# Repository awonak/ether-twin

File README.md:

# Ether Twin

A platform for sharing control voltage and audio over RJ45 shielded network cable

Note: These modules are still a work in progress and may contain errors.

## Ether Twin v1 - Stand-alone

Stand-alone passive desktop version.

Follow the ibom component placement guide [here](https://htmlpreview.github.io/?https://github.com/awonak/ether-twin/blob/main/ether_v1/bom/ibom.html).

Step by step build guide [here](ether_v1/README.md).

## Ether Twin v2 - 3U

Rack mount 3U 10HP version

*Photo Coming Soon*

## Ether Mix - Stand-alone

Stand-alone passive mixer

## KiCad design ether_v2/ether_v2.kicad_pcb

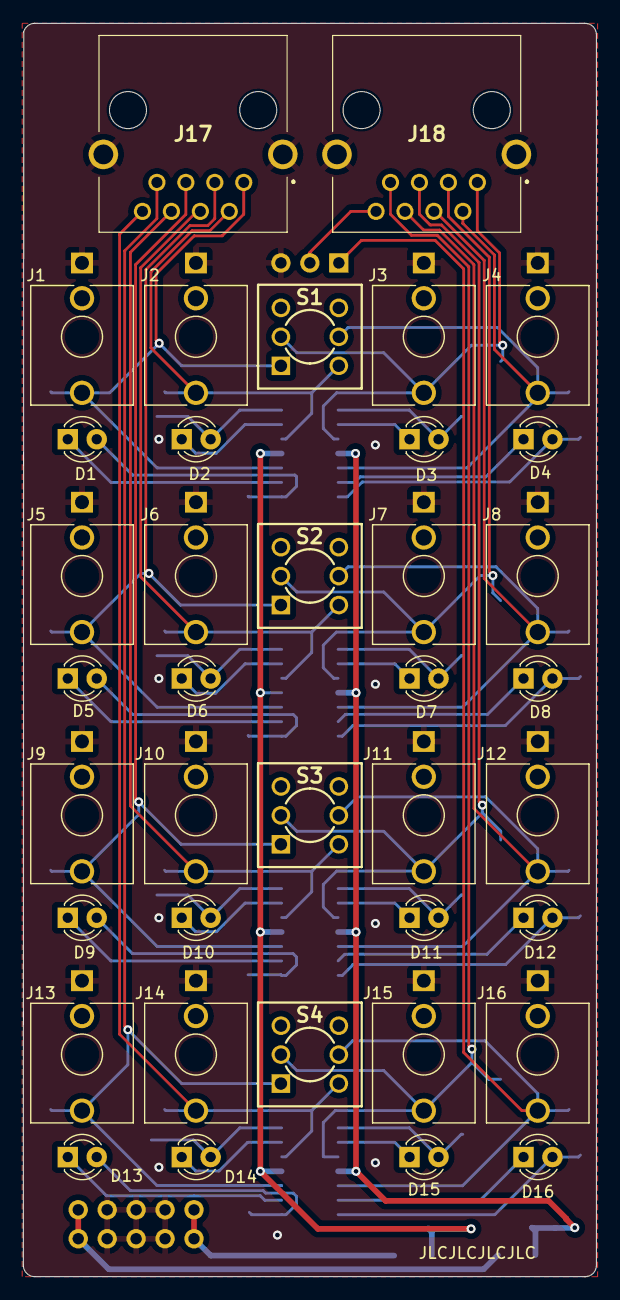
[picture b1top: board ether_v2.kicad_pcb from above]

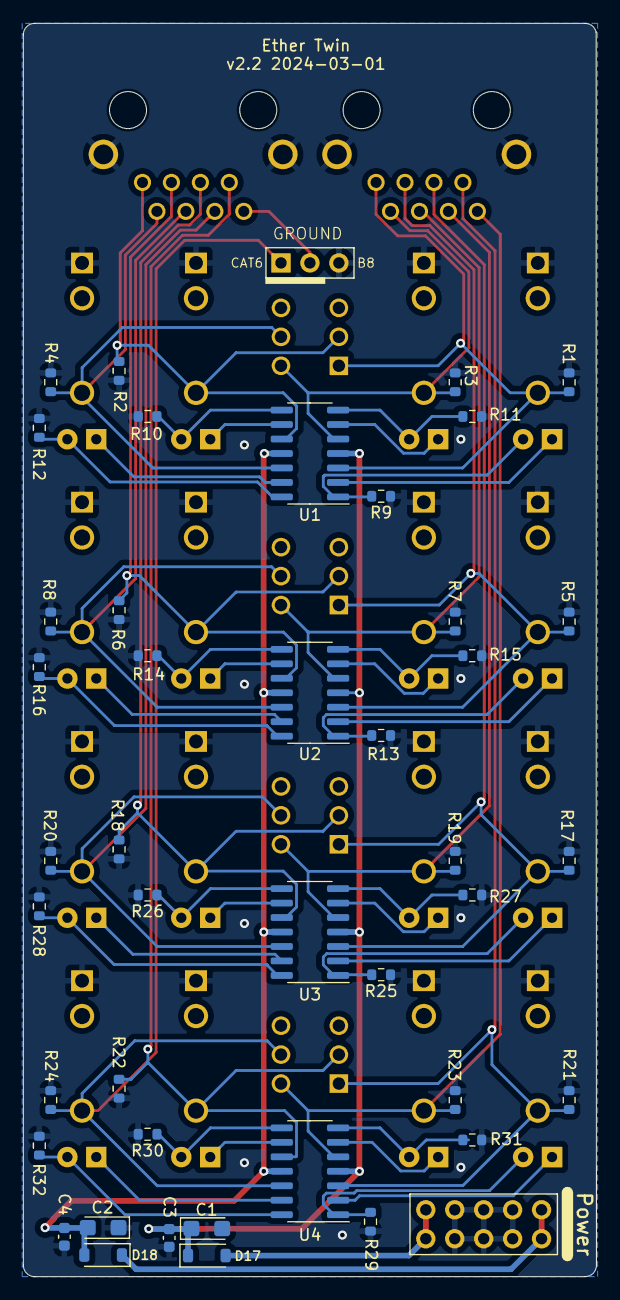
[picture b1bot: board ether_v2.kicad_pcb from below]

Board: 2 copper layers, 50.3 x 110.0 mm, 82 parts (44 on the bottom side), 54 nets.

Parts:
C1, C2: 10uF; CP_EIA-3216-18_Kemet-A
C3, C4: 100nF; C_0603_1608Metric
D1, D2, D3, D4, D5, D6, D7, D8, D9, D10, D11, D12, D13, D14, D15, D16: LED_Dual_Bidirectional; LED_D3.0mm
D17, D18: 1N5817; D_SOD-123
J1, J2, J3, J4, J5, J6, J7, J8, J9, J10, J11, J12, J13, J14, J15, J16: PJ398SM; Jack_3.5mm_QingPu_WQP-PJ398SM_Vertical_CircularHoles_3dModel
J17, J18: SS65100-024F; SS65100024F
J19: Power; Pins_2x05_2.54mm_TH_Europower
J20: Conn_01x03; PinHeader_1x03_P2.54mm_Vertical
R1, R2, R3, R4, R5, R6, R7, R8, R17, R18, R19, R20, R21, R22, R23, R24: 100K; R_0603_1608Metric
R9, R10, R11, R12, R13, R14, R15, R16, R25, R26, R27, R28, R29, R30, R31, R32: 470; R_0603_1608Metric
S1, S2, S3, S4: 2MD1T1B1M2QES
U1, U2, U3, U4: TL074; SO-14_3.9x8.65mm_P1.27mm

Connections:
+12V: C1.1, C3.1, D17.1 (K), U1.4 (V+), U2.4 (V+), U3.4 (V+), U4.4 (V+)
-12V: C2.2, C4.2, D18.2 (A), U1.11 (V-), U2.11 (V-), U3.11 (V-), U4.11 (V-)
A1: J1.T, J17.1, R1.2, S1.1 (A), U1.3 (+)
A2: J2.T, J17.2, R3.2, S1.4 (A), U1.5 (+)
A3: J5.T, J17.3, R5.2, S2.1 (A), U2.3 (+)
A4: J6.T, J17.4, R7.2, S2.4 (A), U2.5 (+)
A5: J9.T, J17.5, R17.2, S3.1 (A), U3.3 (+)
A6: J10.T, J17.6, R19.2, S3.4 (A), U3.5 (+)
A7: J13.T, J17.7, R21.2, S4.1 (A), U4.3 (+)
A8: J14.T, J17.8, R23.2, S4.4 (A), U4.5 (+)
B1: J3.T, J18.1, R2.2, S1.2 (B), U1.10 (+)
B2: J4.T, J18.2, R4.2, S1.5 (B), U1.12 (+)
B3: J7.T, J18.3, R6.2, S2.2 (B), U2.10 (+)
B4: J8.T, J18.4, R8.2, S2.5 (B), U2.12 (+)
B5: J11.T, J18.5, R18.2, S3.2 (B), U3.10 (+)
B6: J12.T, J18.6, R20.2, S3.5 (B), U3.12 (+)
B7: J15.T, J18.7, R22.2, S4.2 (B), U4.10 (+)
B8: J18.8, J20.2
GND: C1.2, C2.1, C3.2, C4.1, J1.S, J2.S, J3.S, J4.S, J5.S, J6.S, J7.S, J8.S, J9.S, J10.S, J11.S, J12.S, J13.S, J14.S, J15.S, J16.S, J17.9, J17.10, J18.9, J18.10, J19.3 (GND), J19.4 (GND), J19.5 (GND), J19.6 (GND), J19.7 (GND), J19.8 (GND), J20.3, R1.1, R2.1, R3.1, R4.1, R5.1, R6.1, R7.1, R8.1, R9.1, R10.2, R11.1, R12.2, R13.1, R14.2, R15.1, R16.2, R17.1, R18.1, R19.1, R20.1, R21.1, R22.1, R23.1, R24.1, R25.1, R26.2, R27.1, R28.2, R29.1, R30.2, R31.1, R32.2
unnamed: D1.2 (A), R9.2, U1.1
unnamed: D1.1 (K), U1.2 (-)
unnamed: D2.2 (A), R11.2, U1.7
unnamed: D2.1 (K), U1.6 (-)
unnamed: D3.2 (A), R10.1, U1.8
unnamed: D3.1 (K), U1.9 (-)
unnamed: D4.2 (A), R12.1, U1.14
unnamed: D4.1 (K), U1.13 (-)
unnamed: D5.2 (A), R13.2, U2.1
unnamed: D5.1 (K), U2.2 (-)
unnamed: D6.2 (A), R15.2, U2.7
unnamed: D6.1 (K), U2.6 (-)
unnamed: D7.2 (A), R14.1, U2.8
unnamed: D7.1 (K), U2.9 (-)
unnamed: D8.2 (A), R16.1, U2.14
unnamed: D8.1 (K), U2.13 (-)
unnamed: D9.2 (A), R25.2, U3.1
unnamed: D9.1 (K), U3.2 (-)
unnamed: D10.2 (A), R27.2, U3.7
unnamed: D10.1 (K), U3.6 (-)
unnamed: D11.2 (A), R26.1, U3.8
unnamed: D11.1 (K), U3.9 (-)
unnamed: D12.2 (A), R28.1, U3.14
unnamed: D12.1 (K), U3.13 (-)
unnamed: D13.2 (A), R29.2, U4.1
unnamed: D13.1 (K), U4.2 (-)
unnamed: D14.2 (A), R31.2, U4.7
unnamed: D14.1 (K), U4.6 (-)
unnamed: D15.2 (A), R30.1, U4.8
unnamed: D15.1 (K), U4.9 (-)
unnamed: D16.2 (A), R32.1, U4.14
unnamed: D16.1 (K), U4.13 (-)
unnamed: D17.2 (A), J19.1 (+12V), J19.2 (+12V)
unnamed: D18.1 (K), J19.9 (-12V), J19.10 (-12V)
unnamed: J16.T, J20.1, R24.2, S4.5 (B), U4.12 (+)

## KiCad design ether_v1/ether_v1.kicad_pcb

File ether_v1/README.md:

# Ether Twin v1

Tutorial Video:
https://youtu.be/pQHyfLVjiQw?si=90aeZab5XTt6bDr_

## Bill of Materials

| Reference(s) | Qty | Value | Supplier Link |
|-|-|-|-|
| J1 - J16  | 16 | Thonkiconn 3.5mm Mono Jack | https://www.thonk.co.uk/shop/thonkiconn/ |
| J17, J18 | 2 | Ethernet Connectors | https://www.mouser.com/ProductDetail/571-1-406541-5 |
| S1, S2, S3, S4 | 4 | DPDT Switch ON-ON | https://www.thonk.co.uk/shop/sub-mini-toggle-switches/ |
| S5 | 1 | 1PDT Slide Swith ON-ON | https://www.mouser.com/ProductDetail/611-JS102011SAQN |

## Build Guide v1.2

### Solder the components to the main PCB

Follow the ibom component placement guide [here](https://htmlpreview.github.io/?https://github.com/awonak/ether-twin/blob/main/ether_v1/bom/ibom.html).

1. Start by soldering the Ground Select switch S5

1. Place the two Ethernet Jacks. Begin by tacking one mounting hole lug on each Ethernet Jack. Press firmly on the jack while heating the tacked solder to ensure a snug fit.

1. Once the Ethernet Jack lugs are soldered and the jacks are flush against the PCB, then proceed to solder the 8 jack pins. (Pro tip; smear a bit of rosin flux against the pins, then drag a large bead of solder across the pins.)

1. Next, place all 16 cv jacks on the PCB. Attach the top panel, and screw nuts on the 4 corner jacks to hold them in place. Now you can flip the module over and lay it down flat while soldering the cv jacks.

1. (v1.2+ only) Remove the top panel and place the 4 toggle switches. Place the top panel back on and screw on the same 4 corner nut jacks and the 4 switch nuts. Flip the module over and solder the 4 toggle switches. (Either carefully rest the module against one side of the toggle switches, or use a third-hand to hold the module.)

### Assemble the enclosure

1. Remove the top panel attached during the previous step. This will make it easier to attach the standoffs later.

1. Start by threading the loger M3 screws through the 4 mounting holes of the bottom panel.

1. Tighten the M3 nut against those screws.

1. Place the components PCB against the nuts, components facing up.

1. Tighten the 10mm nylon standoffs to the bottom panel screws sticking up from the components PCB.

1. Attach the top panel to the component pcb and screw on all 16 cv jack nuts and 4 toggle switch nuts.

1. Screw the shorter M3 screws into the top panel mounting holes and into the standoffs.

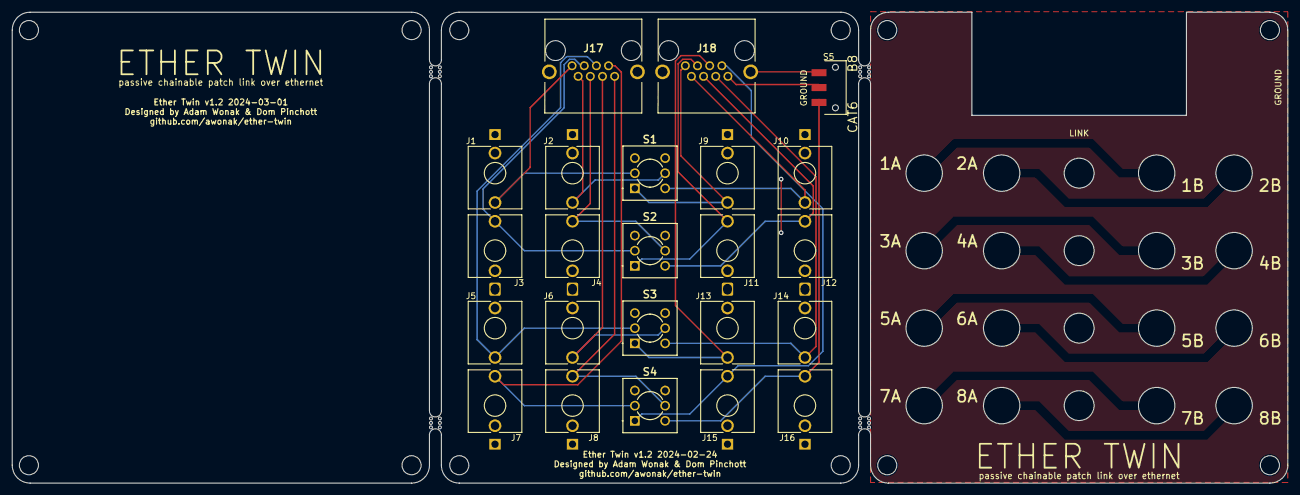
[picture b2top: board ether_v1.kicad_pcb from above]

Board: 2 copper layers, 214.0 x 79.0 mm, 27 parts (0 on the bottom side), 18 nets.

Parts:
J1, J2, J3, J4, J5, J6, J7, J8, J9, J10, J11, J12, J13, J14, J15, J16: AudioJack2_SwitchT; Jack_3.5mm_QingPu_WQP-PJ398SM_Vertical_CircularHoles_3dModel
J17, J18: 1-406541-5; 14065415
MH: VAL**; mouse-bite-2mm-slot
MH#2, MH#3, MH#4: VAL**; mouse-bite-2mm-slot
S1, S2, S3, S4: 2MD1T1B1M2QES
S5: JS102011SAQN; SW_JS102011SAQN

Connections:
A1: J1.T, J17.1, S1.2 (B)
A2: J2.T, J17.2, S1.5 (B)
A3: J3.T, J17.3, S2.2 (B)
A4: J4.T, J17.4, S2.5 (B)
A5: J5.T, J17.5, S3.2 (B)
A6: J6.T, J17.6, S3.5 (B)
A7: J7.T, J17.7, S4.2 (B)
A8: J8.T, J17.8, S4.5 (B)
B1: J9.T, J18.1, S1.1 (A)
B2: J10.T, J18.2, S1.4 (A)
B3: J11.T, J18.3, S2.1 (A)
B4: J12.T, J18.4, S2.4 (A)
B5: J13.T, J18.5, S3.1 (A)
B6: J14.T, J18.6, S3.4 (A)
B7: J15.T, J18.7, S4.1 (A)
B8: J18.8, S5.2
GND: J1.S, J2.S, J3.S, J4.S, J7.S, J8.S, J9.S, J10.S, J11.S, J12.S, J15.S, J16.S, J17.9, J17.10, J18.9, J18.10, S5.3
unnamed: J16.T, S4.4 (A), S5.1

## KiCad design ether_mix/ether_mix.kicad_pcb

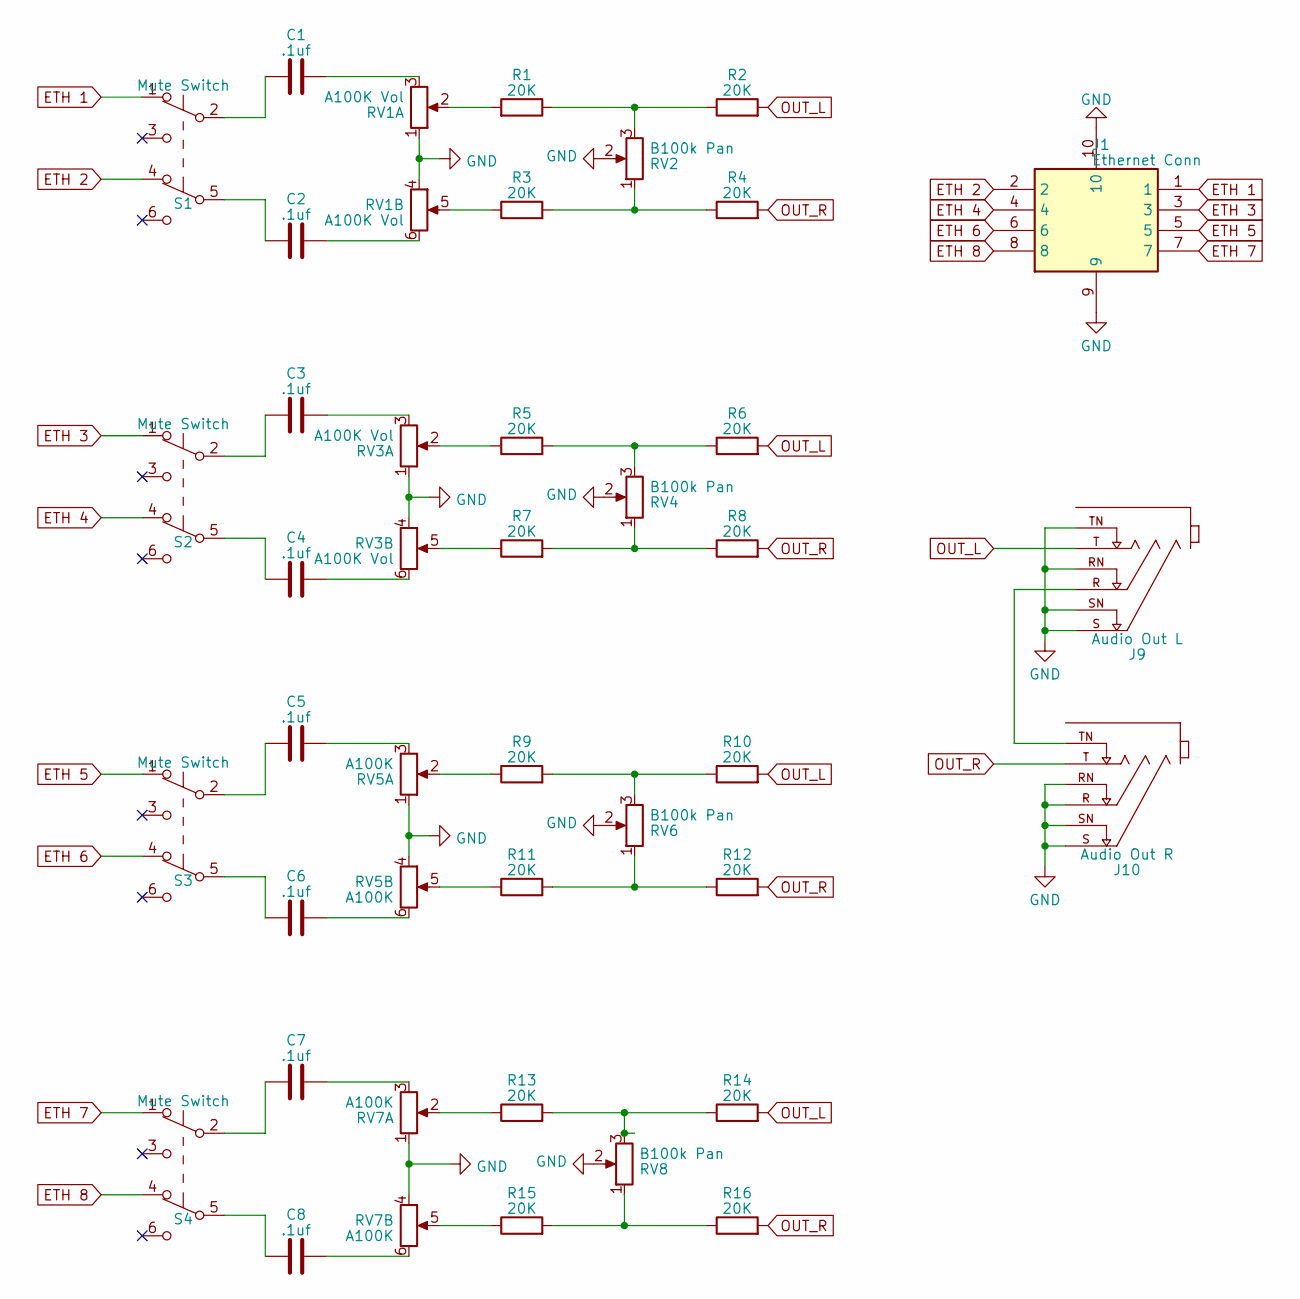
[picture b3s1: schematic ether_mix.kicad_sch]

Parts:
C1, C2, C3, C4, C5, C6, C7, C8: .1uf; C_0603_1608Metric
J1: Ethernet Conn; 14065415; Mouser Part Number 571-1-406541-5
J9: Audio Out L; NEUTRIK_NRJ6HF; PARTREV 19.02.2021
J10: Audio Out R; NEUTRIK_NRJ6HF; PARTREV 19.02.2021
R1, R2, R3, R4, R5, R6, R7, R8, R9, R10, R11, R12, R13, R14, R15, R16: 20K; R_0603_1608Metric
RV1, RV3: A100K Vol; Potentiometer_Alpha_RD902F-40-00D_Dual_Vertical_CircularHol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
RV2, RV4, RV6, RV8: B100k Pan; Potentiometer_Alpha_RD901F-40-00D_Single_Vertical
RV5, RV7: A100K; Potentiometer_Alpha_RD902F-40-00D_Dual_Vertical_CircularHol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
S1, S2, S3, S4: Mute Switch; 2MD1T1B1M2QES; Mouser Part Number 118-2MD1T1B1M2QES

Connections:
ETH 1: J1.1, S1.1 (A)
ETH 2: J1.2, S1.4 (A)
ETH 3: J1.3, S2.1 (A)
ETH 4: J1.4, S2.4 (A)
ETH 5: J1.5, S3.1 (A)
ETH 6: J1.6, S3.4 (A)
ETH 7: J1.7, S4.1 (A)
ETH 8: J1.8, S4.4 (A)
GND: J1.9, J1.10, J9.RN, J9.S, J9.SN, J9.TN, J10.R, J10.RN, J10.S, J10.SN, RV1.1, RV1.4, RV2.2, RV3.1, RV3.4, RV4.2, RV5.1, RV5.4, RV6.2, RV7.1, RV7.4, RV8.2
unnamed: C1.1, S1.2 (B)
unnamed: C1.2, RV1.3
unnamed: C2.1, S1.5 (B)
unnamed: C2.2, RV1.6
unnamed: C3.1, S2.2 (B)
unnamed: C3.2, RV3.3
unnamed: C4.1, S2.5 (B)
unnamed: C4.2, RV3.6
unnamed: C5.1, S3.2 (B)
unnamed: C5.2, RV5.3
unnamed: C6.1, S3.5 (B)
unnamed: C6.2, RV5.6
unnamed: C7.1, S4.2 (B)
unnamed: C7.2, RV7.3
unnamed: C8.1, S4.5 (B)
unnamed: C8.2, RV7.6
unnamed: J9.R, J10.TN
unnamed: R1.1, R2.1, RV2.3
unnamed: R1.2, RV1.2
unnamed: R3.1, RV1.5
unnamed: R3.2, R4.1, RV2.1
unnamed: R5.1, RV3.2
unnamed: R5.2, R6.1, RV4.3
unnamed: R7.1, RV3.5
unnamed: R7.2, R8.1, RV4.1
unnamed: R9.1, RV5.2
unnamed: R9.2, R10.1, RV6.3
unnamed: R11.1, RV5.5
unnamed: R11.2, R12.1, RV6.1
unnamed: R13.1, RV7.2
unnamed: R13.2, R14.1, RV8.3
unnamed: R15.1, RV7.5
unnamed: R15.2, R16.1, RV8.1
OUT_L: J9.T, R2.2, R6.2, R10.2, R14.2
OUT_R: J10.T, R4.2, R8.2, R12.2, R16.2

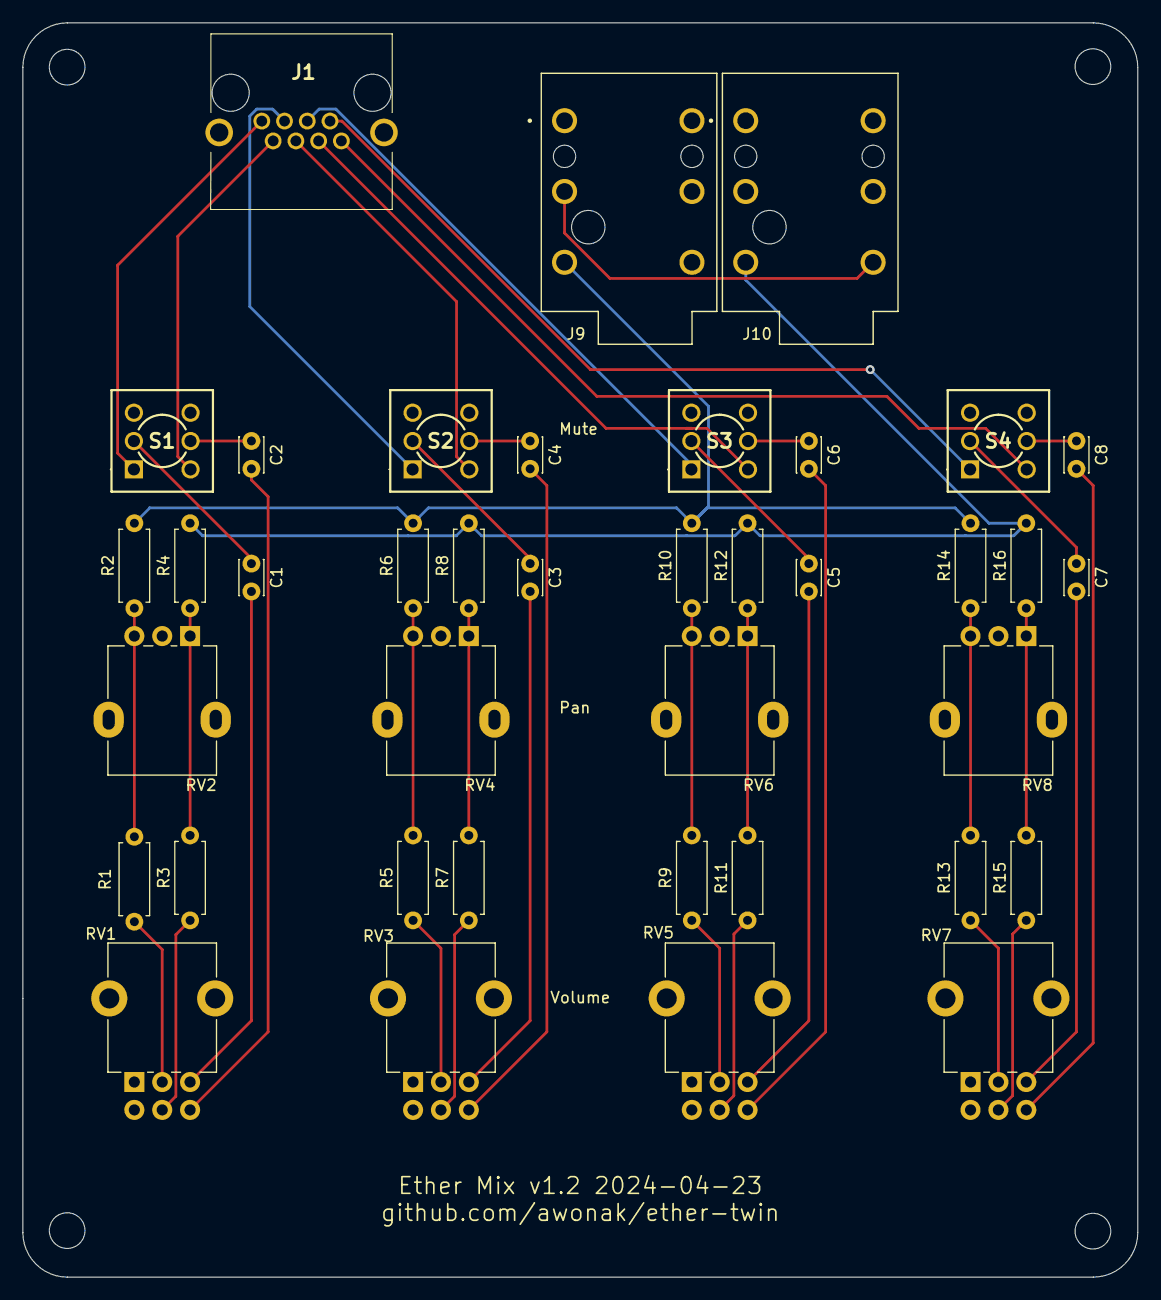
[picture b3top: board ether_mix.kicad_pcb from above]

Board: 2 copper layers, 100.0 x 112.5 mm, 43 parts (0 on the bottom side), 44 nets.

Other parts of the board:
H1, H2, H3, H4: MountingHole; MountingHole_3.2mm_M3

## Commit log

2024-02-28 resize images
2024-03-03 Add Ether Twin v1 README, bom, schematic.
2024-03-14 add schematic for Ether Twin v2
2024-03-17 Fix incorrect placement of ground and led resistor. Fixes Odd wiring of LED in schematic. #1
2024-03-17 Update pcb revision silkscreen.
2024-04-24 Add Ether Twin v2 schematic
2024-04-24 Add Ether Mix
2024-04-24 Ether v1 panel label update
2024-04-24 fix bad merge
2025-07-01 Add ether twin v1 tutorial video
